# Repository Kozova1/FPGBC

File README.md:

# FPGBC - Field Programmable Game Boy Cartridge
This is a project for an open-source cartridge for the Game Boy (Color).
Each cartridge contains an iCE40UP5K FPGA, interfacing through level shifters with the Game Boy and through an MCP2210 with your PC.

## Licensing
The hardware is licensed under the [BSD 3-clause license](./hardware/LICENSE),
being a modified version of [tsuraraGB](https://github.com/rniwase/tsuraraGB/).

All non-hardware code (including FPGA code, python tooling, etc.) is licensed under the [GPLv3](./LICENSE)

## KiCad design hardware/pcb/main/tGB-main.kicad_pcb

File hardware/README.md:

# Gaslight Cart (modified tsuraraGB cartridge)
Nintendo Gameboy cartridge-shaped FPGA (Lattice iCE40UP5K) development board

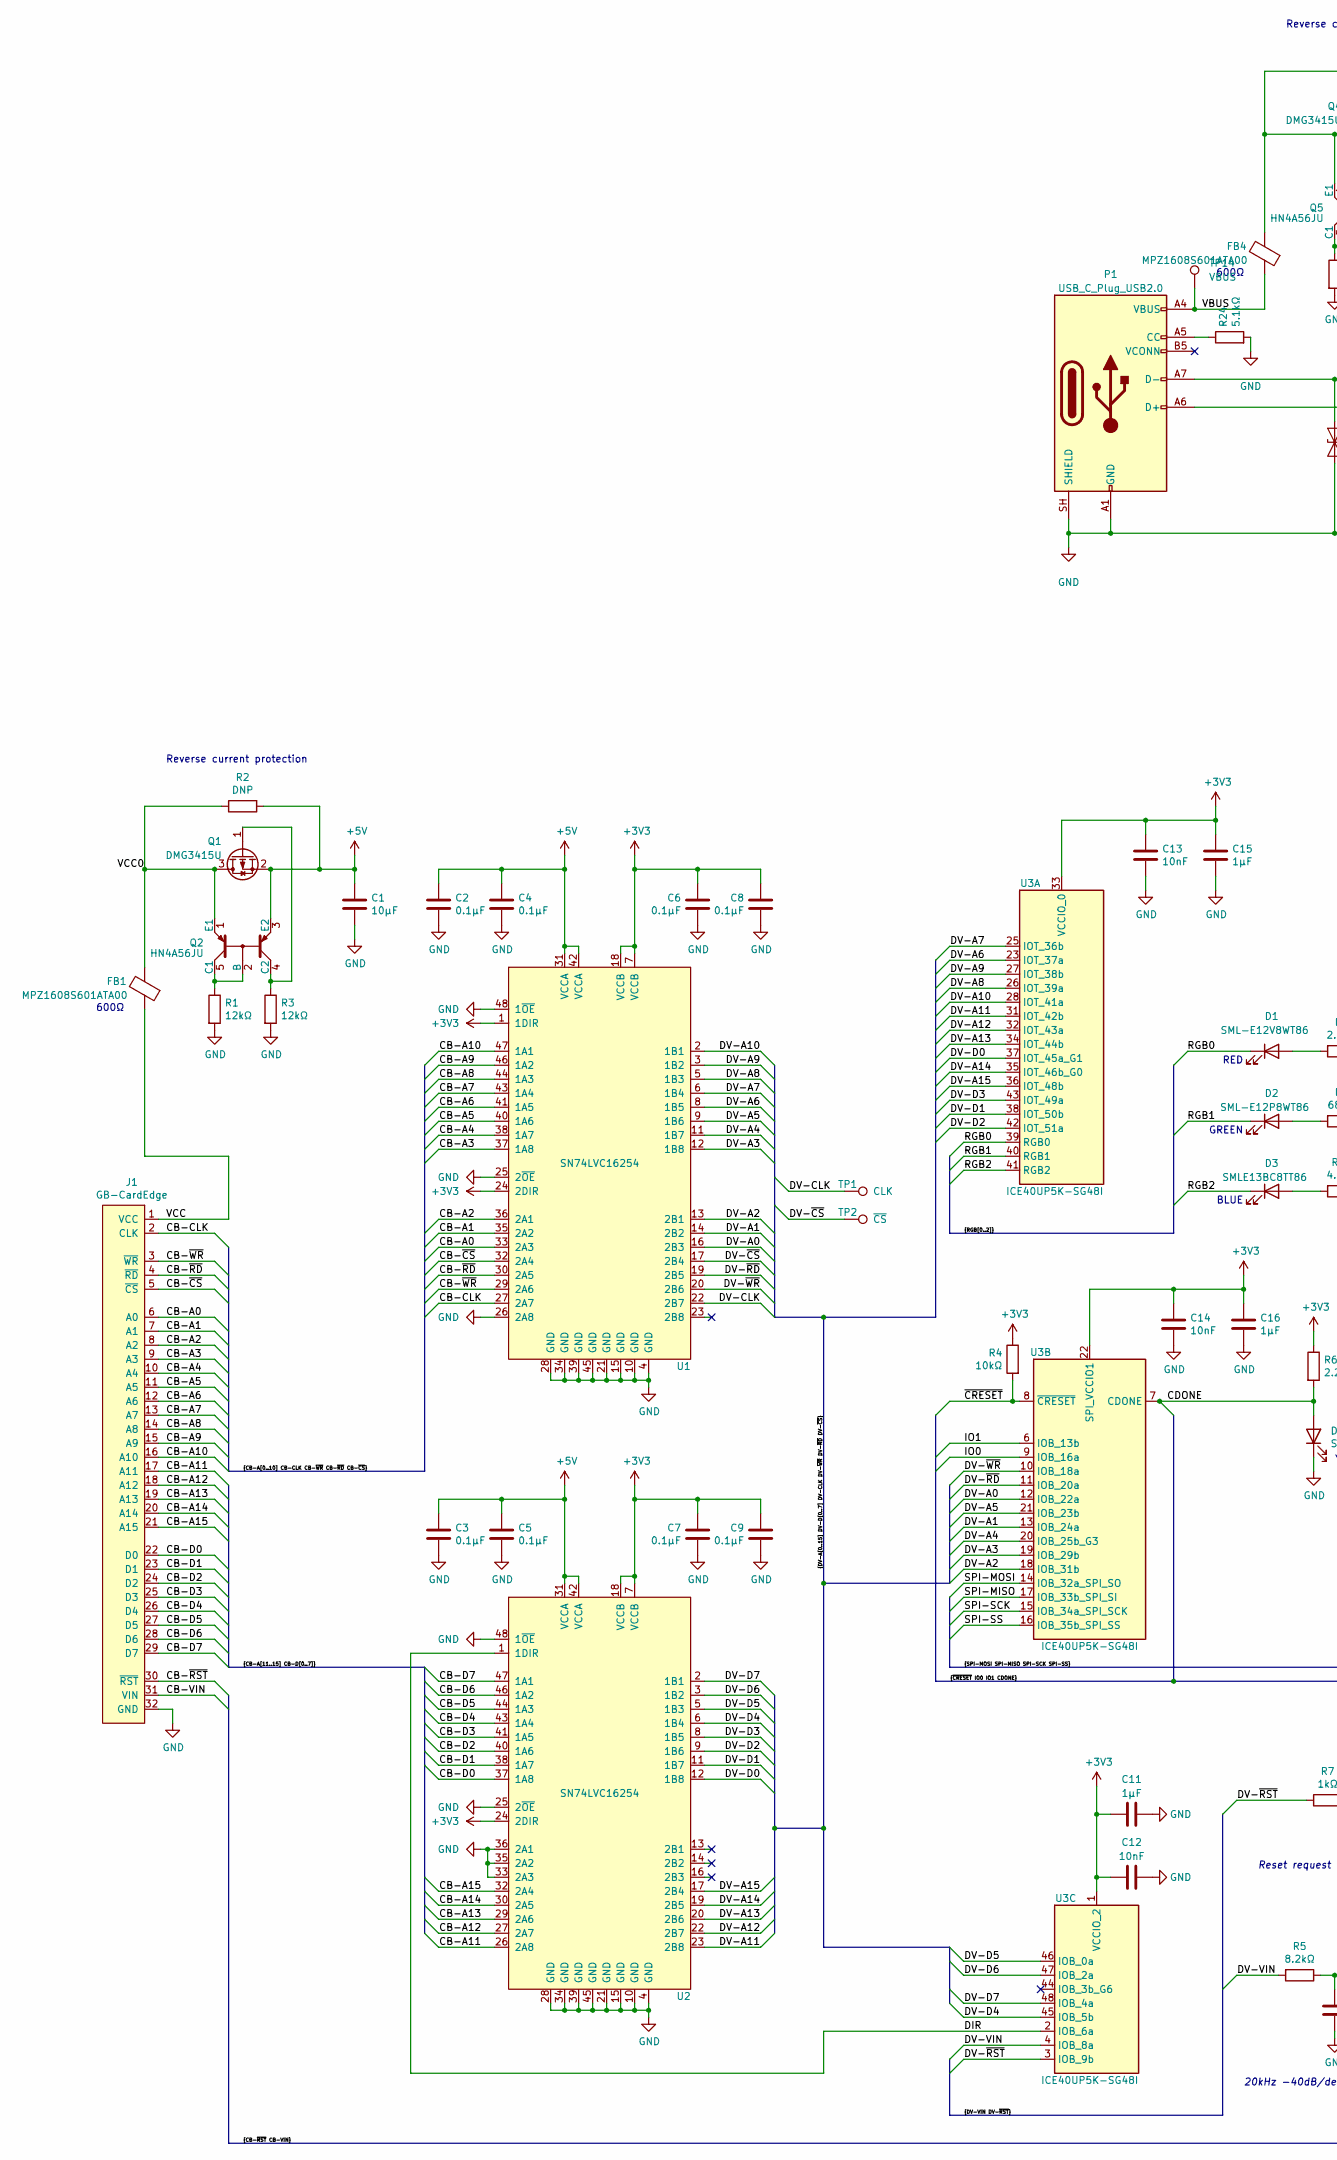
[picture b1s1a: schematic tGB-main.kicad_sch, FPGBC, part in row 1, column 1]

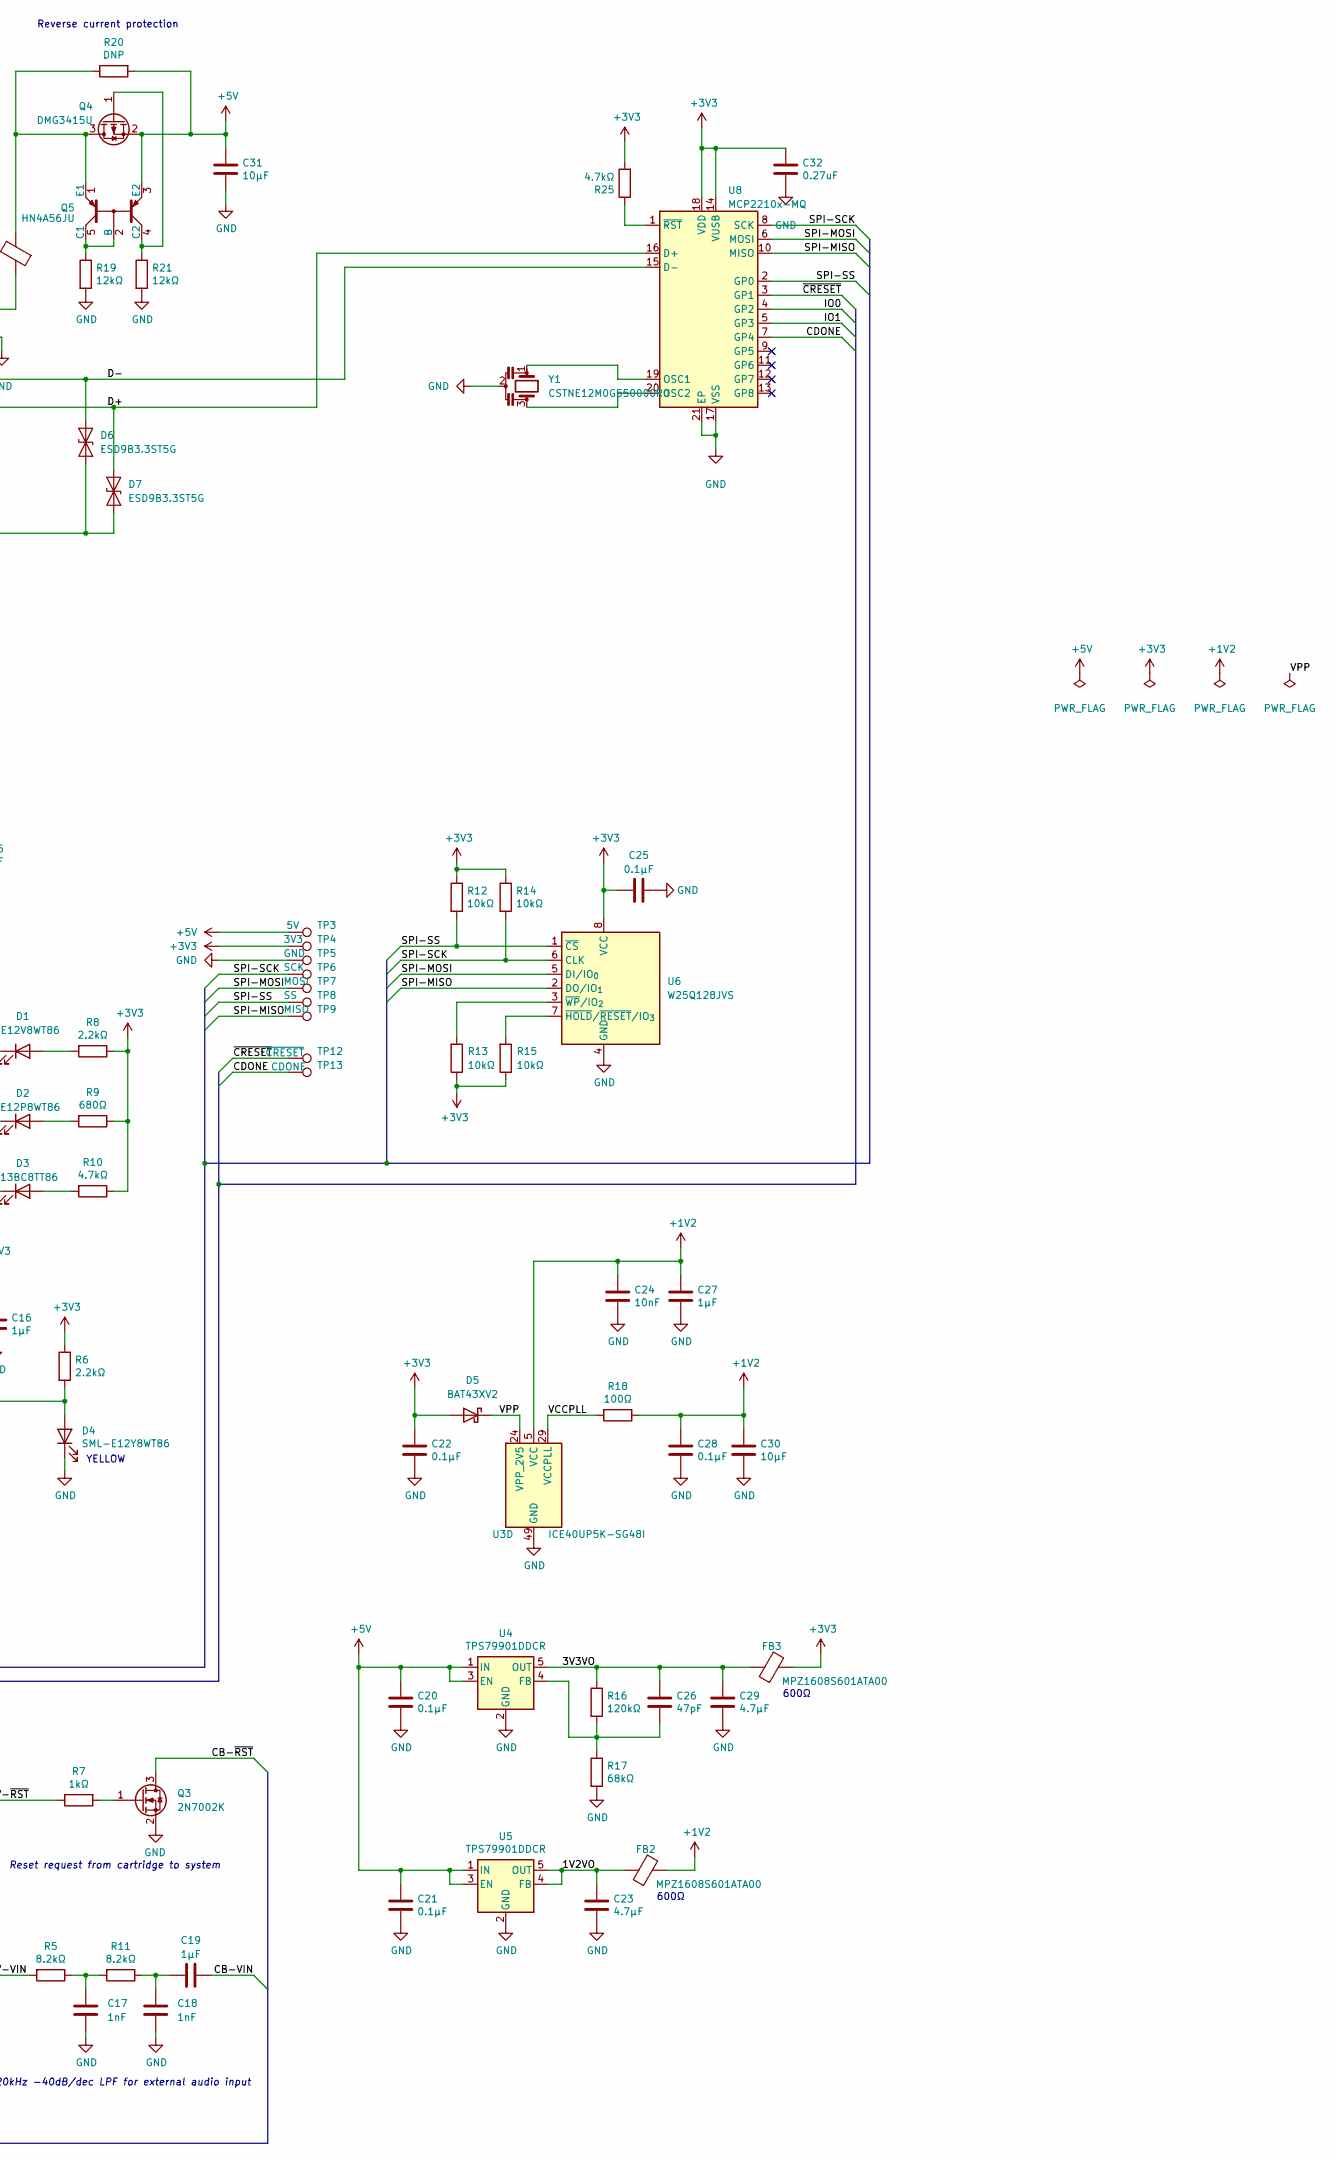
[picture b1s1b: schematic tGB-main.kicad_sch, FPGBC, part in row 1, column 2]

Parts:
C1, C30, C31: 10μF; C_0603_1608Metric
C2, C3, C4, C5, C6, C7, C8, C9, C20, C21, C22, C25, C28: 0.1μF; C_0402_1005Metric
C11, C15, C16, C19, C27: 1μF; C_0402_1005Metric
C12, C13, C14, C24: 10nF; C_0402_1005Metric
C17, C18: 1nF; C_0402_1005Metric
C23, C29: 4.7μF; C_0402_1005Metric
C26: 47pF; C_0402_1005Metric
C32: 0.27uF; C_0603_1608Metric
D1: SML-E12V8WT86; LED_0603_1608Metric_Castellated
D2: SML-E12P8WT86; LED_0603_1608Metric_Castellated
D3: SMLE13BC8TT86; LED_0603_1608Metric_Castellated
D4: SML-E12Y8WT86; LED_0603_1608Metric_Castellated
D5: BAT43XV2; D_SOD-523
D6, D7: ESD9B3.3ST5G; D_SOD-923
FB1, FB2, FB3, FB4: MPZ1608S601ATA00; L_0603_1608Metric
J1: GB-CardEdge
P1: USB_C_Plug_USB2.0; USB_C_Receptacle_GCT_USB4105-xx-A_16P_TopMnt_Horizontal
Q1, Q4: DMG3415U; SOT-23
Q2, Q5: HN4A56JU; SC-74A-5_1.55x2.9mm_P0.95mm
Q3: 2N7002K; SOT-23
R1, R3, R19, R21: 12kΩ; R_0402_1005Metric
R2, R20: DNP; R_0603_1608Metric
R4, R12, R13, R14, R15: 10kΩ; R_0402_1005Metric
R5, R11: 8.2kΩ; R_0402_1005Metric
R6, R8: 2.2kΩ; R_0402_1005Metric
R7: 1kΩ; R_0402_1005Metric
R9: 680Ω; R_0402_1005Metric
R10, R25: 4.7kΩ; R_0402_1005Metric
R16: 120kΩ; R_0402_1005Metric
R17: 68kΩ; R_0402_1005Metric
R18: 100Ω; R_0402_1005Metric
R24: 5.1kΩ; R_0402_1005Metric
TP1: CLK; TestPoint_Pad_D1.0mm
TP2: ~{CS}; TestPoint_Pad_D1.0mm
TP3: 5V; TestPoint_Pad_D1.0mm
TP4: 3V3; TestPoint_Pad_D1.0mm
TP5: GND; TestPoint_Pad_D1.0mm
TP6: SCK; TestPoint_Pad_D1.0mm
TP7: MOSI; TestPoint_Pad_D1.0mm
TP8: SS; TestPoint_Pad_D1.0mm
TP9: MISO; TestPoint_Pad_D1.0mm
TP12: ~{CRESET}; TestPoint_Pad_D1.0mm
TP13: CDONE; TestPoint_Pad_D1.0mm
TP14: VBUS; TestPoint_Pad_D1.0mm
U1, U2: SN74LVC16254; TSSOP-48_6.1x12.5mm_P0.5mm
U3: ICE40UP5K-SG48I; QFN-48-1EP_7x7mm_P0.5mm_EP5.6x5.6mm
U4, U5: TPS79901DDCR; SOT-23-5
U6: W25Q128JVS; SOIC-8_5.3x5.3mm_P1.27mm
U8: MCP2210x-MQ; QFN-20-1EP_5x5mm_P0.65mm_EP3.35x3.35mm
Y1: CSTNE12M0G550000R0; CSTNE10M0G55A000R0

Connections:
+1V2: C24.1, C27.1, C28.1, C30.1, FB2.2, R18.1, U3.5 (VCC), U3.30 (VCC)
+3V3: C6.1, C7.1, C8.1, C9.1, C11.1, C12.1, C13.1, C14.1, C15.1, C16.1, C22.1, C25.1, C32.1, D5.2 (A), FB3.2, R4.1, R6.1, R8.1, R9.1, R10.1, R12.1, R13.1, R14.1, R15.1, R25.2, TP4.1 (1_1), U1.1 (1DIR), U1.7 (VCCB), U1.18 (VCCB), U1.24 (2DIR), U2.7 (VCCB), U2.18 (VCCB), U2.24 (2DIR), U3.1 (VCCIO_2), U3.22 (SPI_VCCIO1), U3.33 (VCCIO_0), U6.8 (VCC), U8.14 (VUSB), U8.18 (VDD); also elsewhere on the board
+5V: C1.1, C2.1, C3.1, C4.1, C5.1, C20.1, C21.1, C31.1, Q1.2 (S), Q2.3 (E2), Q4.2 (S), Q5.3 (E2), R2.2, R20.2, TP3.1 (1_1), U1.31 (VCCA), U1.42 (VCCA), U2.31 (VCCA), U2.42 (VCCA), U4.1 (IN), U4.3 (EN), U5.1 (IN), U5.3 (EN)
/1V2VO: C23.1, FB2.1, U5.4 (FB), U5.5 (OUT)
/3V3VO: C26.1, C29.1, FB3.1, R16.1, U4.5 (OUT)
/CB-A0: J1.6 (A0), U1.33 (2A3)
/CB-A1: J1.7 (A1), U1.35 (2A2)
/CB-A2: J1.8 (A2), U1.36 (2A1)
/CB-A3: J1.9 (A3), U1.37 (1A8)
/CB-A4: J1.10 (A4), U1.38 (1A7)
/CB-A5: J1.11 (A5), U1.40 (1A6)
/CB-A6: J1.12 (A6), U1.41 (1A5)
/CB-A7: J1.13 (A7), U1.43 (1A4)
/CB-A8: J1.14 (A8), U1.44 (1A3)
/CB-A9: J1.15 (A9), U1.46 (1A2)
/CB-A10: J1.16 (A10), U1.47 (1A1)
/CB-A11: J1.17 (A11), U2.26 (2A8)
/CB-A12: J1.18 (A12), U2.27 (2A7)
/CB-A13: J1.19 (A13), U2.29 (2A6)
/CB-A14: J1.20 (A14), U2.30 (2A5)
/CB-A15: J1.21 (A15), U2.32 (2A4)
/CB-CLK: J1.2 (CLK), U1.27 (2A7)
/CB-D0: J1.22 (D0), U2.37 (1A8)
/CB-D1: J1.23 (D1), U2.38 (1A7)
/CB-D2: J1.24 (D2), U2.40 (1A6)
/CB-D3: J1.25 (D3), U2.41 (1A5)
/CB-D4: J1.26 (D4), U2.43 (1A4)
/CB-D5: J1.27 (D5), U2.44 (1A3)
/CB-D6: J1.28 (D6), U2.46 (1A2)
/CB-D7: J1.29 (D7), U2.47 (1A1)
/CB-VIN: C19.1, J1.31 (VIN)
/CB-~CS: J1.5 (~CS), U1.32 (2A4)
/CB-~RD: J1.4 (~RD), U1.30 (2A5)
/CB-~RST: J1.30 (~RST), Q3.3 (D)
/CB-~WR: J1.3 (~WR), U1.29 (2A6)
/CDONE: D4.2 (A), R6.2, TP13.1 (1_1), U3.7 (CDONE), U8.7 (GP4)
/D+: D7.2 (A2), P1.A6 (D+), U8.16 (D+)
/D-: D6.2 (A2), P1.A7 (D-), U8.15 (D-)
/DIR: U2.1 (1DIR), U3.2 (IOB_6a)
/DV-A0: U1.16 (2B3), U3.12 (IOB_22a)
/DV-A1: U1.14 (2B2), U3.13 (IOB_24a)
/DV-A2: U1.13 (2B1), U3.18 (IOB_31b)
/DV-A3: U1.12 (1B8), U3.19 (IOB_29b)
/DV-A4: U1.11 (1B7), U3.20 (IOB_25b_G3)
/DV-A5: U1.9 (1B6), U3.21 (IOB_23b)
/DV-A6: U1.8 (1B5), U3.23 (IOT_37a)
/DV-A7: U1.6 (1B4), U3.25 (IOT_36b)
/DV-A8: U1.5 (1B3), U3.26 (IOT_39a)
/DV-A9: U1.3 (1B2), U3.27 (IOT_38b)
/DV-A10: U1.2 (1B1), U3.28 (IOT_41a)
/DV-A11: U2.23 (2B8), U3.31 (IOT_42b)
/DV-A12: U2.22 (2B7), U3.32 (IOT_43a)
/DV-A13: U2.20 (2B6), U3.34 (IOT_44b)
/DV-A14: U2.19 (2B5), U3.35 (IOT_46b_G0)
/DV-A15: U2.17 (2B4), U3.36 (IOT_48b)
/DV-CLK: TP1.1 (1_1), U1.22 (2B7)
/DV-D0: U2.12 (1B8), U3.37 (IOT_45a_G1)
/DV-D1: U2.11 (1B7), U3.38 (IOT_50b)
/DV-D2: U2.9 (1B6), U3.42 (IOT_51a)
/DV-D3: U2.8 (1B5), U3.43 (IOT_49a)
/DV-D4: U2.6 (1B4), U3.45 (IOB_5b)
/DV-D5: U2.5 (1B3), U3.46 (IOB_0a)
/DV-D6: U2.3 (1B2), U3.47 (IOB_2a)
/DV-D7: U2.2 (1B1), U3.48 (IOB_4a)
/DV-VIN: R5.2, U3.4 (IOB_8a)
/DV-~CS: TP2.1 (1_1), U1.17 (2B4)
/DV-~RD: U1.19 (2B5), U3.11 (IOB_20a)
/DV-~RST: R7.1, U3.3 (IOB_9b)
/DV-~WR: U1.20 (2B6), U3.10 (IOB_18a)
/IO0: U3.9 (IOB_16a), U8.4 (GP2)
/IO1: U3.6 (IOB_13b), U8.5 (GP3)
/RGB0: D1.1 (K), U3.39 (RGB0)
/RGB1: D2.1 (K), U3.40 (RGB1)
/RGB2: D3.1 (K), U3.41 (RGB2)
/SPI-MISO: TP9.1 (1_1), U3.17 (IOB_33b_SPI_SI), U6.2 (DO/IO_{1}), U8.10 (MISO)
/SPI-MOSI: TP7.1 (1_1), U3.14 (IOB_32a_SPI_SO), U6.5 (DI/IO_{0}), U8.6 (MOSI)
/SPI-SCK: R14.2, TP6.1 (1_1), U3.15 (IOB_34a_SPI_SCK), U6.6 (CLK), U8.8 (SCK)
/SPI-SS: R12.2, TP8.1 (1_1), U3.16 (IOB_35b_SPI_SS), U6.1 (~CS), U8.2 (GP0)
/VBUS: FB4.1, P1.A4 (VBUS), P1.A9 (VBUS), P1.B4 (VBUS), P1.B9 (VBUS), TP14.1 (1_1)
/VCC: FB1.1, J1.1 (VCC)
/VCC0: FB1.2, Q1.3 (D), Q2.1 (E1), R2.1
/VCCPLL: R18.2, U3.29 (VCCPLL)
/VPP: D5.1 (K), U3.24 (VPP_2V5)
/~CRESET: R4.2, TP12.1 (1_1), U3.8 (~CRESET), U8.3 (GP1)
GND: C1.2, C2.2, C3.2, C4.2, C5.2, C6.2, C7.2, C8.2, C9.2, C11.2, C12.2, C13.2, C14.2, C15.2, C16.2, C17.2, C18.2, C20.2, C21.2, C22.2, C23.2, C24.2, C25.2, C27.2, C28.2, C29.2, C30.2, C31.2, C32.2, D4.1 (K), D6.1 (A1), D7.1 (A1), J1.32 (GND), P1.A1 (GND), P1.A12 (GND), P1.B1 (GND), P1.B12 (GND), P1.SH (SHIELD), Q3.2 (S), R1.2, R3.2, R17.2, R19.2, R21.2, R24.2, TP5.1 (1_1), U1.4 (GND), U1.10 (GND), U1.15 (GND), U1.21 (GND), U1.25 (2~OE), U1.26 (2A8), U1.28 (GND), U1.34 (GND), U1.39 (GND), U1.45 (GND), U1.48 (1~OE), U2.4 (GND), U2.10 (GND), U2.15 (GND), U2.21 (GND), U2.25 (2~OE), U2.28 (GND), U2.33 (2A3), U2.34 (GND), U2.35 (2A2), U2.36 (2A1), U2.39 (GND), U2.45 (GND), U2.48 (1~OE), U3.49 (GND), U4.2 (GND), U5.2 (GND), U6.4 (GND), U8.17 (VSS), U8.21 (EP), Y1.2; also elsewhere on the board
unnamed: C17.1, R5.1, R11.2
unnamed: C18.1, C19.2, R11.1
unnamed: D1.2 (A), R8.2
unnamed: D2.2 (A), R9.2
unnamed: D3.2 (A), R10.2
unnamed: P1.A5 (CC), R24.1
unnamed: Q1.1 (G), Q2.4 (C2), R3.1
unnamed: Q2.2 (B), Q2.5 (C1), R1.1
unnamed: Q3.1 (G), R7.2
unnamed: FB4.2, Q4.3 (D), Q5.1 (E1), R20.1
unnamed: Q4.1 (G), Q5.4 (C2), R21.1
unnamed: Q5.2 (B), Q5.5 (C1), R19.1
unnamed: C26.2, R16.2, R17.1, U4.4 (FB)
unnamed: R15.2, U6.7 (~HOLD/~RESET/IO_{3})
unnamed: R13.2, U6.3 (~WP/IO_{2})
unnamed: U8.19 (OSC1), Y1.1
unnamed: U8.20 (OSC2), Y1.3
unnamed: R25.1, U8.1 (~RST)

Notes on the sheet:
Reverse current protection
GREEN
600Ω
YELLOW
RED
Reset request from cartridge to system
BLUE
20kHz -40dB/dec LPF for external audio input

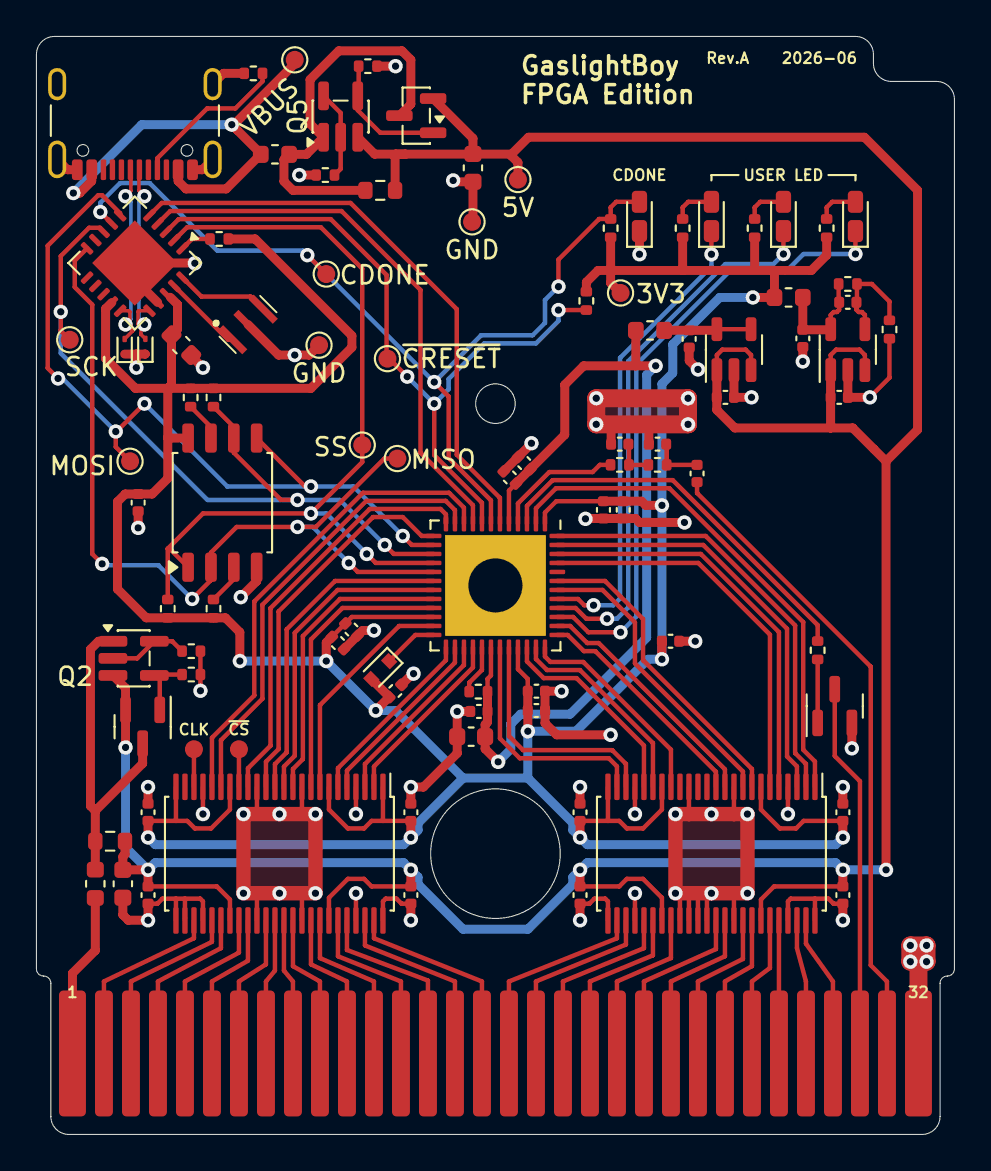
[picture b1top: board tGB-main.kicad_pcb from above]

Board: 2 copper layers, 51.0 x 61.0 mm, 94 parts (0 on the bottom side), 103 nets.

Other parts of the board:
C10: 0.1μF; C_0402_1005Metric
TP10: GND; TestPoint_Pad_D1.0mm

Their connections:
+3V3: C10.1; also elsewhere on the board
GND: C10.2, TP10.1 (1_1); also elsewhere on the board

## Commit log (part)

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2026-06-30 Add source files
2026-06-30 Fix readme

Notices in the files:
hardware/pcb/main/tGB-main.kicad_sch:
Copyright (c) 2026, Ryohei Niwase
Licensed under BSD 3-Clause License
